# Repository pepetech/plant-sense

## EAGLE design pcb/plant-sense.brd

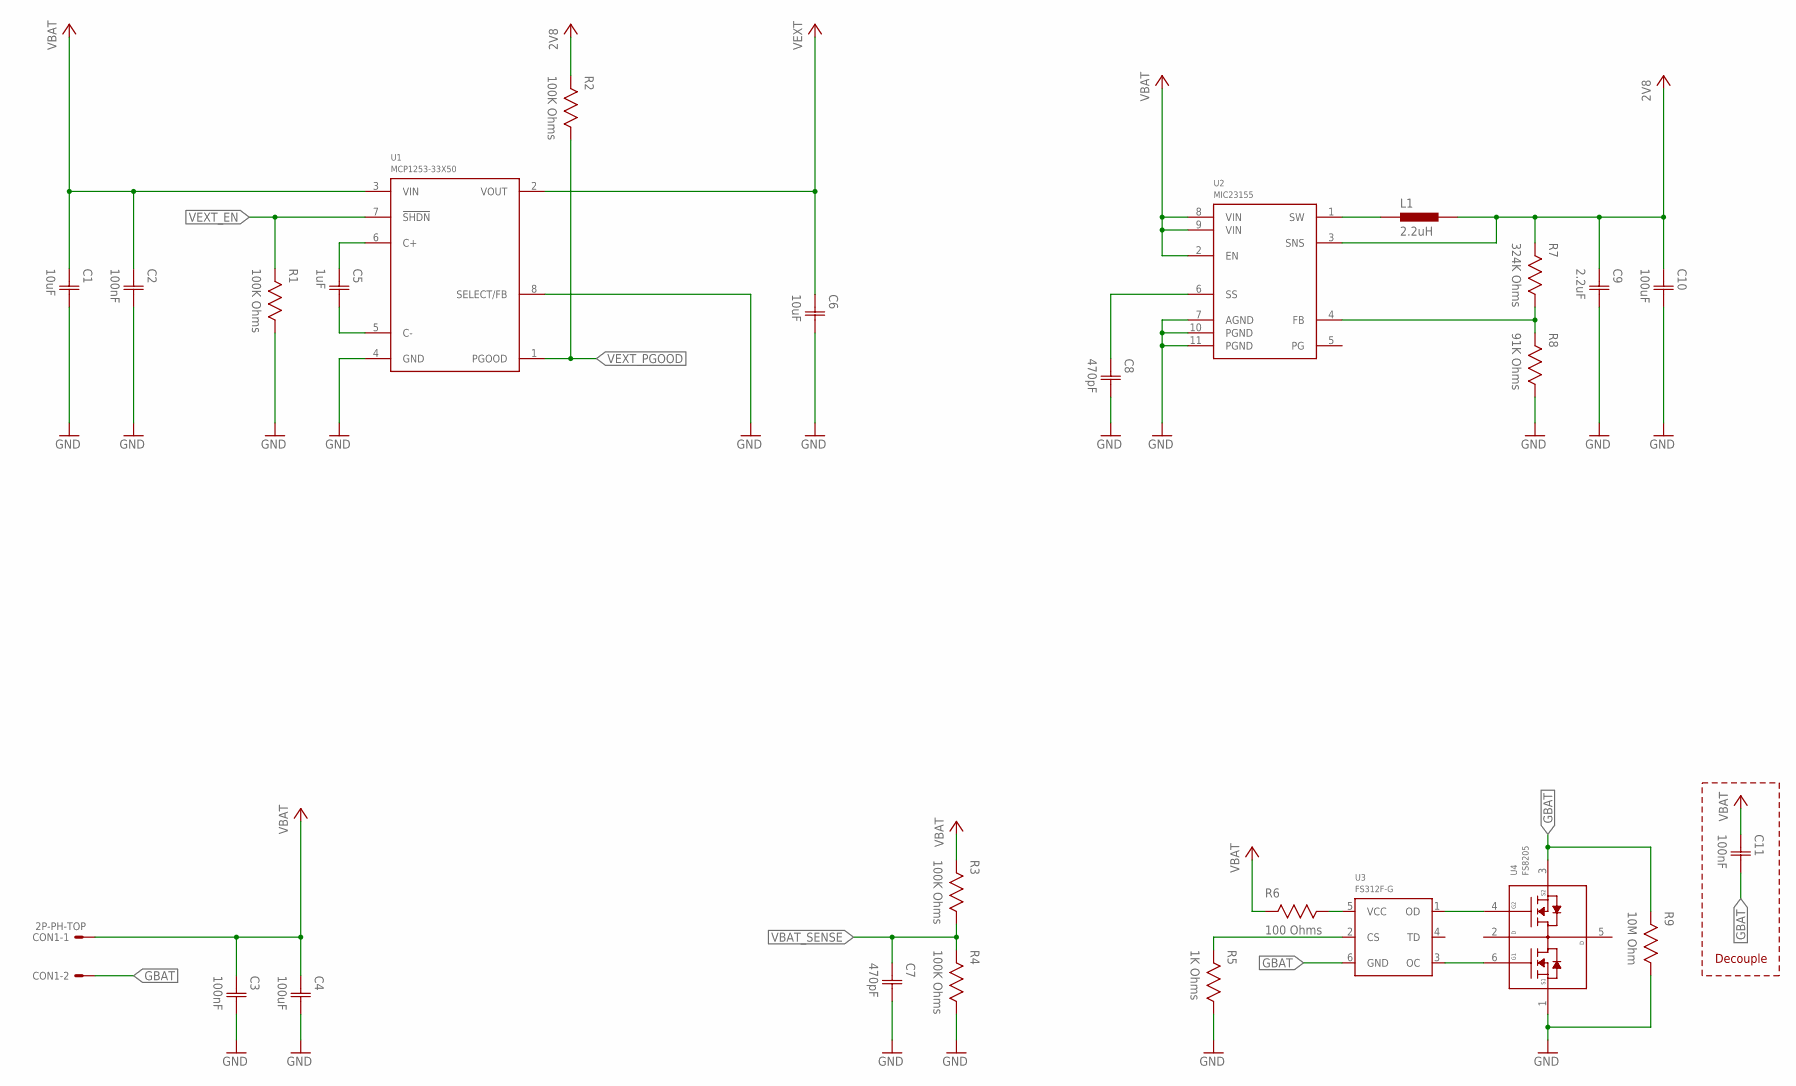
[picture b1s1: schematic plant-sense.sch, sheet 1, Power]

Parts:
C1, C6: 10uF; CAP0603
C2, C3, C11: 100nF; CAP0603
C4, C10: 100uF; CAP1206
C5: 1uF; CAP0603
C7, C8: 470pF; CAP0603
C9: 2.2uF; CAP0603
CON1: 2P-PH-TOP; PH-02-TOP
L1: 2.2uH; IND0805
R1, R2, R3, R4: 100K Ohms; RES0603
R5: 1K Ohms; RES0603
R6: 100 Ohms; RES0603
R7: 324K Ohms; RES0603
R8: 91K Ohms; RES0603
R9: 10M Ohm; RES0603
U1: MCP1253-33X50; MSOP8
U2: MIC23155; DFN10
U3: FS312F-G; SOT23-6
U4: FS8205; SOT23-6

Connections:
2V8: C9.1 (C1), C10.1 (C1), L1.2, R2.2, R7.2, U2.3 (SNS); also elsewhere on the board
GBAT: C11.2 (C2), CON1.2, R9.2, U3.6 (GND), U4.3 (S2)
GND: C1.2 (C2), C2.2 (C2), C3.2 (C2), C4.2 (C2), C6.2 (C2), C7.2 (C2), C8.2 (C2), C9.2 (C2), C10.2 (C2), R1.1, R4.1, R5.1, R8.1, R9.1, U1.4 (GND), U1.8 (SELECT/FB), U2.7 (AGND), U2.10 (PGND), U2.11 (PGND), U4.1 (S1); also elsewhere on the board
unnamed: C5.2 (C2), U1.5 (C-)
unnamed: C5.1 (C1), U1.6 (C+)
unnamed: L1.1, U2.1 (SW)
unnamed: R7.1, R8.2, U2.4 (FB)
unnamed: C8.1 (C1), U2.6 (SS)
unnamed: U3.3 (OC), U4.6 (G1)
unnamed: U3.1 (OD), U4.4 (G2)
unnamed: R6.1, U3.5 (VCC)
unnamed: R5.2, U3.2 (CS)
VBAT: C1.1 (C1), C2.1 (C1), C3.1 (C1), C4.1 (C1), C11.1 (C1), CON1.1, R3.2, R6.2, U1.3 (VIN), U2.2 (EN), U2.8 (VIN), U2.9 (VIN)
VBAT_SENSE: C7.1 (C1), R3.1, R4.2; also elsewhere on the board
VEXT: C6.1 (C1), U1.2 (VOUT); also elsewhere on the board
VEXT_EN: R1.2, U1.7 (!SHDN); also elsewhere on the board
VEXT_PGOOD: R2.1, U1.1 (PGOOD); also elsewhere on the board

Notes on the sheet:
Decouple

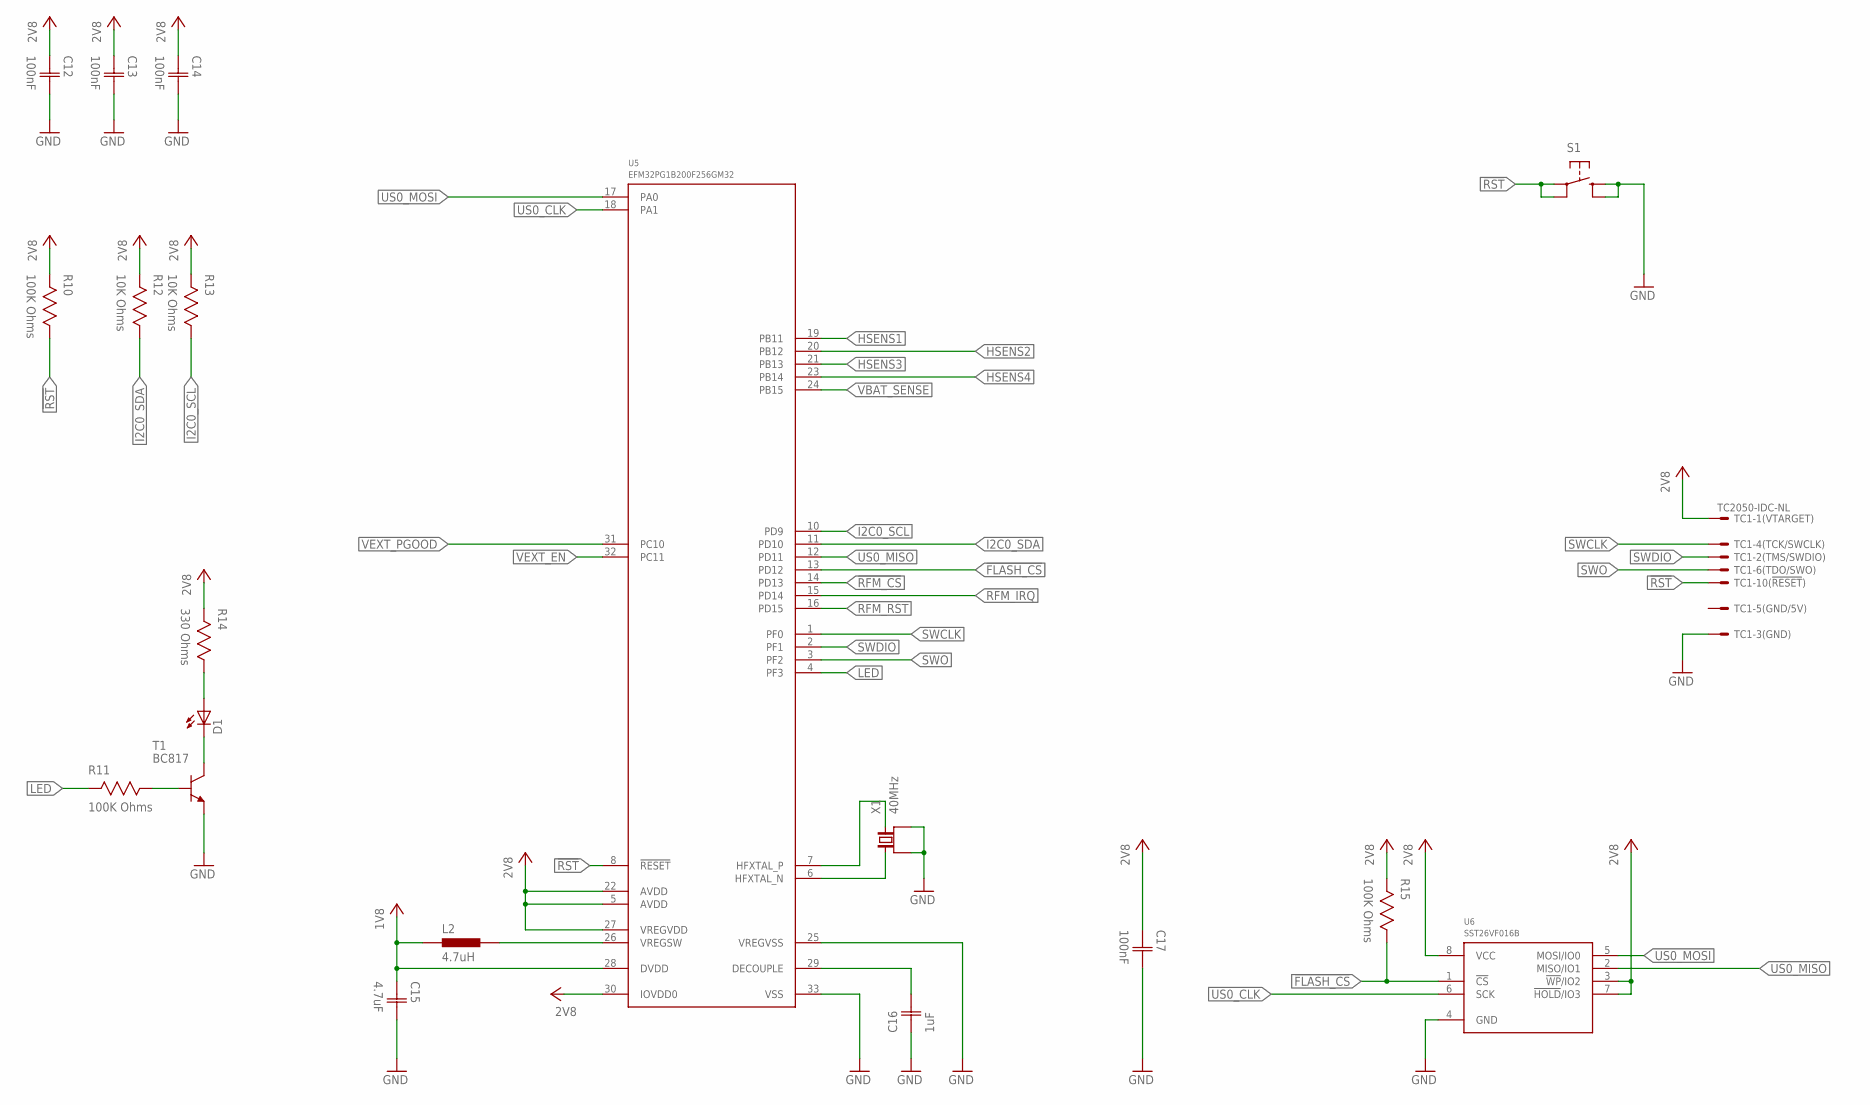
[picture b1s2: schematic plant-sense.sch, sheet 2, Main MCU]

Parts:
C12, C13, C14, C17: 100nF; CAP0603
C15: 4.7uF; CAP0603
C16: 1uF; CAP0603
D1: LED1206; 1206
L2: 4.7uH; IND0603
R10, R11, R15: 100K Ohms; RES0603
R12, R13: 10K Ohms; RES0603
R14: 330 Ohms; RES0603
S1: TAC_SWITCHSMD; TAC_SW_SMD_RESET
T1: BC817; SOT23
TC1: TC2050-IDC-NL
U5: EFM32PG1B200F256GM32; QFN32_0.5P
U6: SST26VF016B; WSOIC8
X1: 40MHz; 4-SMD-3225

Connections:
1V8: C15.1 (C1), L2.1, U5.28 (DVDD)
2V8: C12.1 (C1), C13.1 (C1), C14.1 (C1), C17.1 (C1), R10.2, R12.2, R13.2, R14.2, R15.2, TC1.1, U5.5 (AVDD), U5.22 (AVDD), U5.27 (VREGVDD), U5.30 (IOVDD0), U6.3 (!WP!/IO2), U6.7 (!HOLD!/IO3), U6.8 (VCC); also elsewhere on the board
!FLASH_CS: R15.1, U5.13 (PD12), U6.1 (!CS!)
!RFM_CS: U5.14 (PD13); also elsewhere on the board
!RST: R10.1, S1.1, S1.2, TC1.10, U5.8 (!RESET)
GND: C12.2 (C2), C13.2 (C2), C14.2 (C2), C15.2 (C2), C16.1 (C1), C17.2 (C2), S1.3, S1.4, T1.2 (E), TC1.3, U5.25 (VREGVSS), U5.33 (VSS), U6.4 (GND), X1.1 (GND), X1.3 (GND); also elsewhere on the board
HSENS1: U5.19 (PB11); also elsewhere on the board
HSENS2: U5.20 (PB12); also elsewhere on the board
HSENS3: U5.21 (PB13); also elsewhere on the board
HSENS4: U5.23 (PB14); also elsewhere on the board
I2C0_SCL: R13.1, U5.10 (PD9); also elsewhere on the board
I2C0_SDA: R12.1, U5.11 (PD10); also elsewhere on the board
LED: R11.2, U5.4 (PF3)
unnamed: R11.1, T1.1 (B)
unnamed: D1.C, T1.3 (C)
unnamed: U5.6 (HFXTAL_N), X1.2 (1)
unnamed: U5.7 (HFXTAL_P), X1.4 (2)
unnamed: D1.A, R14.1
unnamed: L2.2, U5.26 (VREGSW)
unnamed: C16.2 (C2), U5.29 (DECOUPLE)
RFM_IRQ: U5.15 (PD14); also elsewhere on the board
RFM_RST: U5.16 (PD15); also elsewhere on the board
SWCLK: TC1.4, U5.1 (PF0)
SWDIO: TC1.2, U5.2 (PF1)
SWO: TC1.6, U5.3 (PF2)
US0_CLK: U5.18 (PA1), U6.6 (SCK); also elsewhere on the board
US0_MISO: U5.12 (PD11), U6.2 (MISO/IO1); also elsewhere on the board
US0_MOSI: U5.17 (PA0), U6.5 (MOSI/IO0); also elsewhere on the board
VBAT_SENSE: U5.24 (PB15); also elsewhere on the board
VEXT_EN: U5.32 (PC11); also elsewhere on the board
VEXT_PGOOD: U5.31 (PC10); also elsewhere on the board

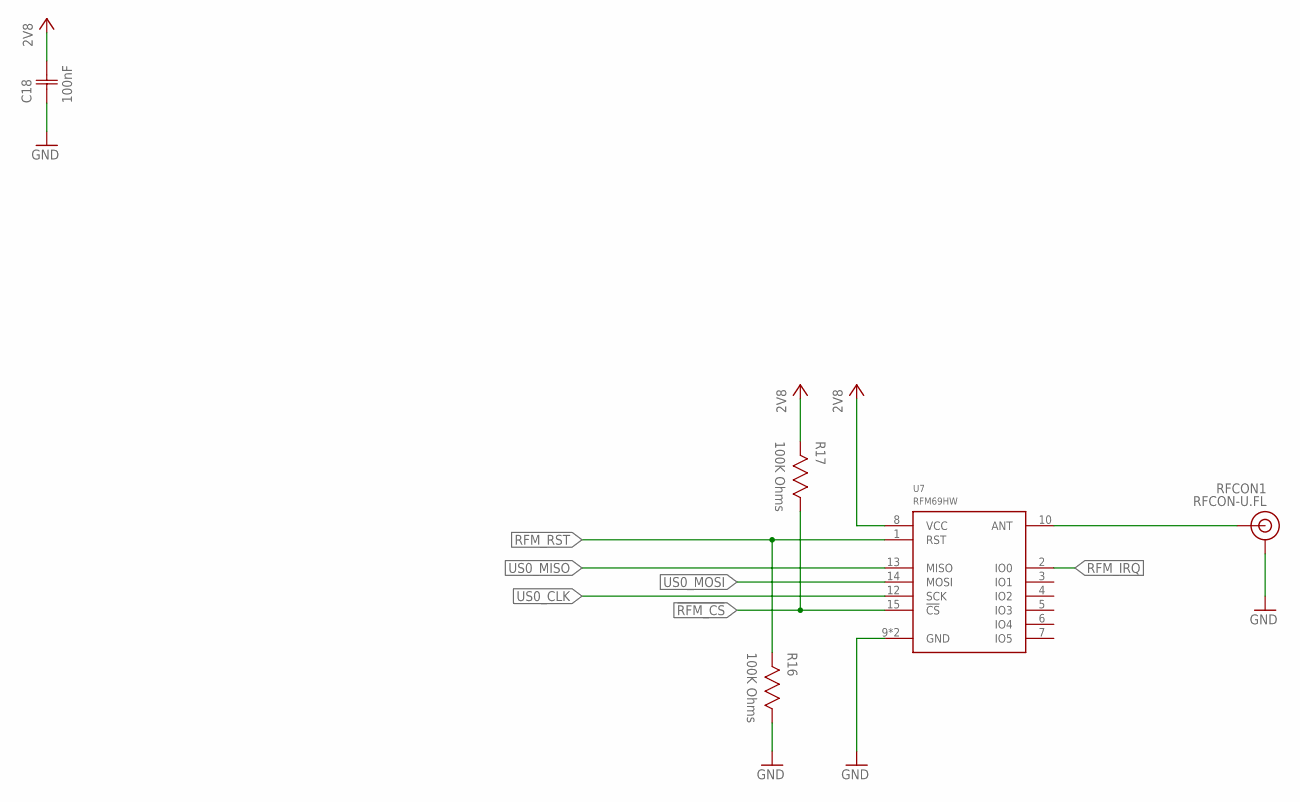
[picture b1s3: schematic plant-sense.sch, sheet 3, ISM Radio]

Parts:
C18: 100nF; CAP0603
R16, R17: 100K Ohms; RES0603
RFCON1: RFCON-U.FL; U.FL
U7: RFM69HW; RFM69XW-XXXS2

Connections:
2V8: C18.2 (C2), R17.2, U7.8 (VCC); also elsewhere on the board
!RFM_CS: R17.1, U7.15 (!CS); also elsewhere on the board
GND: C18.1 (C1), R16.1, RFCON1.P$1 (GND), RFCON1.P$2 (GND), U7.9 (GND), U7.11 (GND); also elsewhere on the board
unnamed: RFCON1.P$3 (SIGNAL), U7.10 (ANT)
RFM_IRQ: U7.2 (IO0); also elsewhere on the board
RFM_RST: R16.2, U7.1 (RST); also elsewhere on the board
US0_CLK: U7.12 (SCK); also elsewhere on the board
US0_MISO: U7.13 (MISO); also elsewhere on the board
US0_MOSI: U7.14 (MOSI); also elsewhere on the board

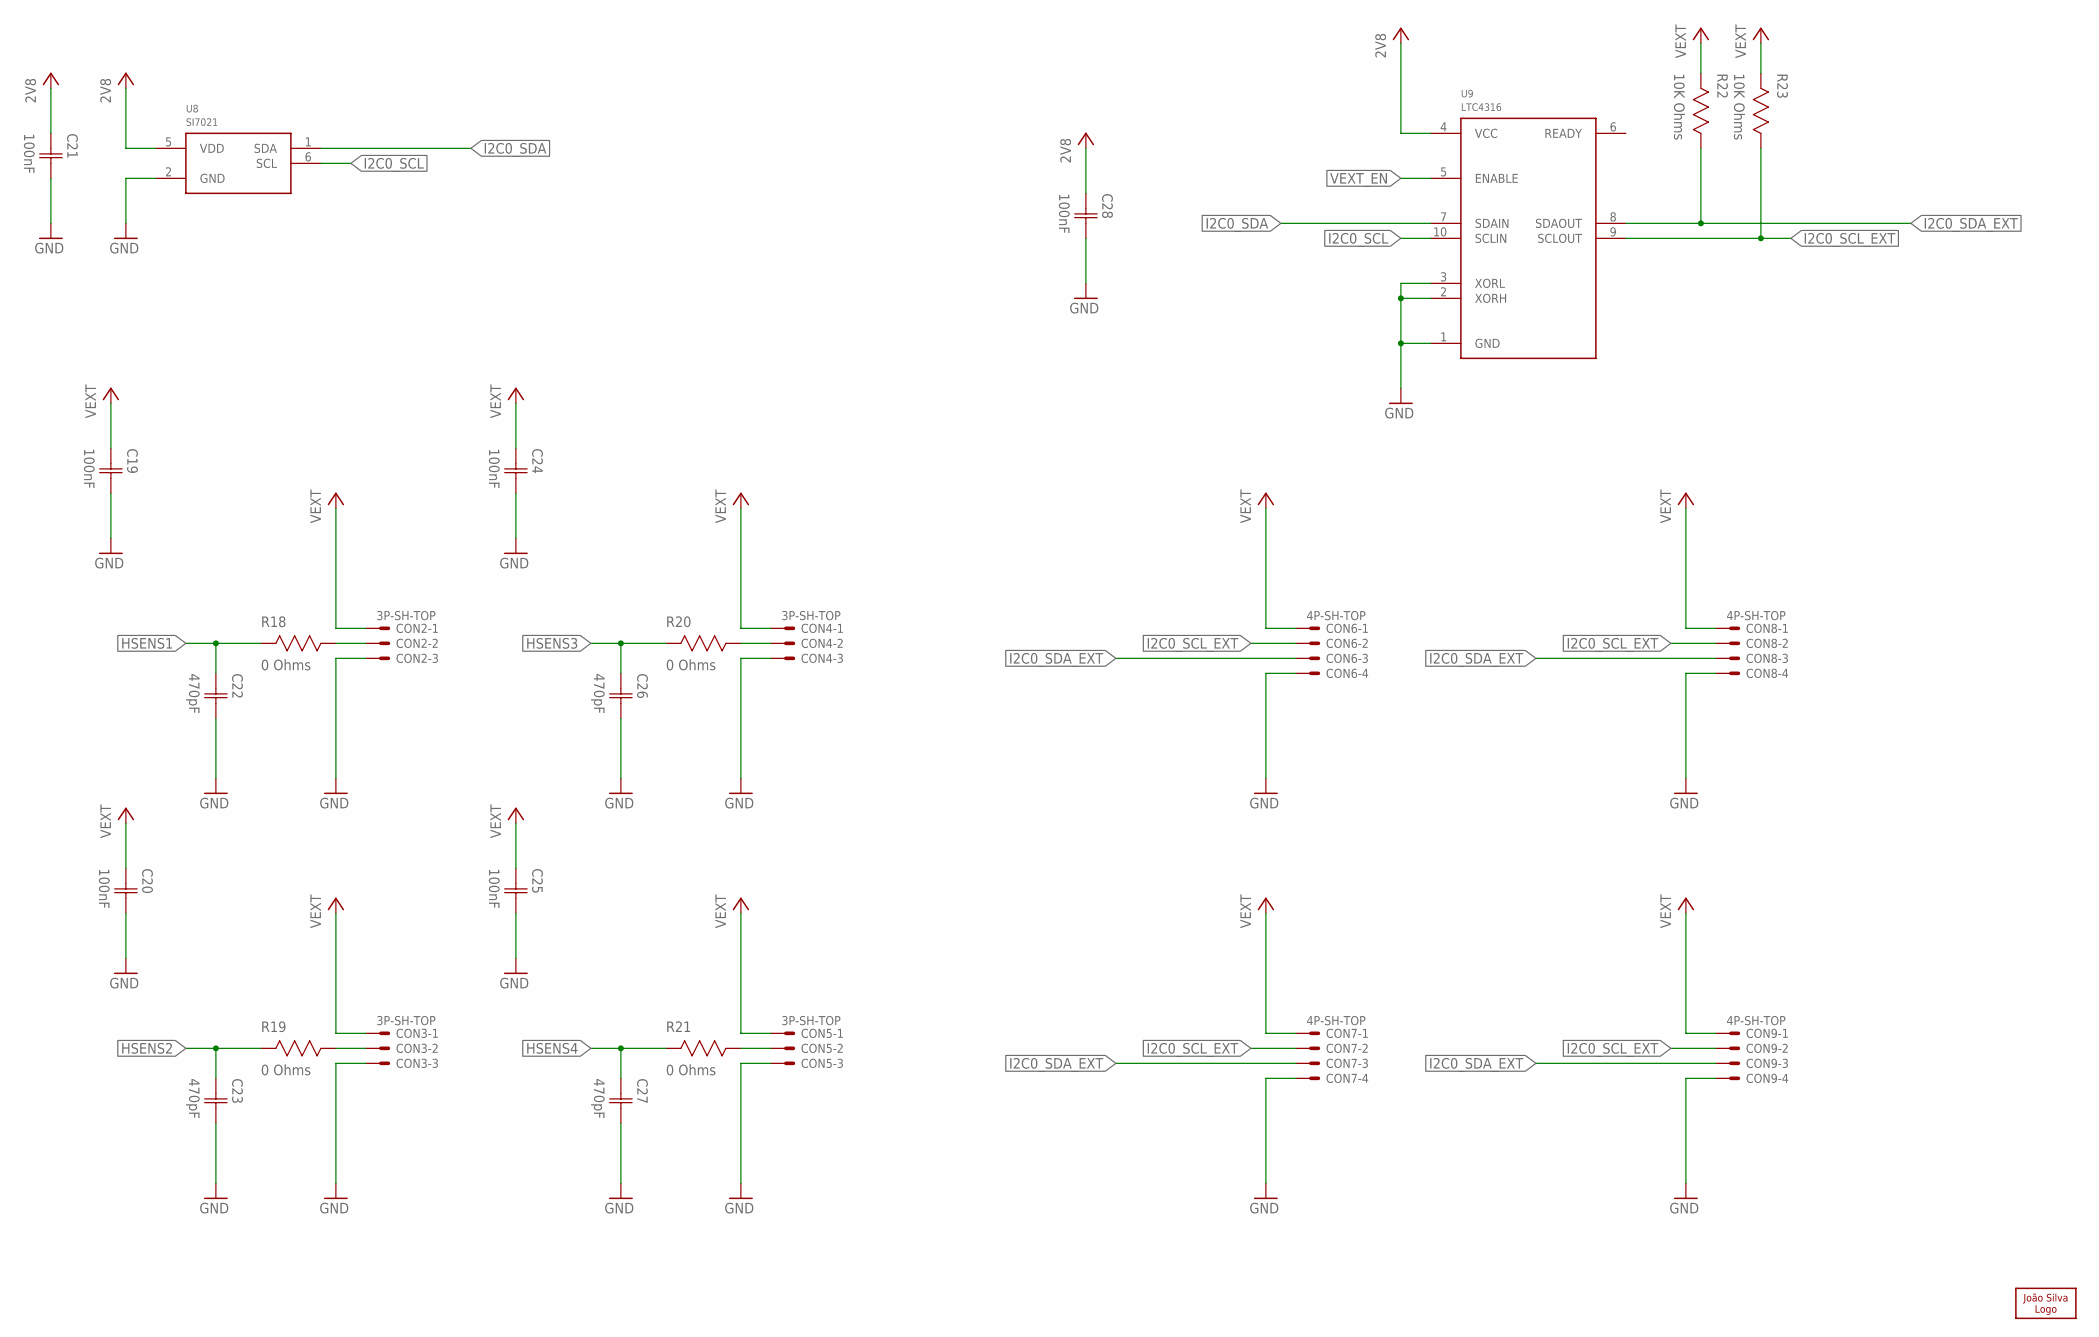
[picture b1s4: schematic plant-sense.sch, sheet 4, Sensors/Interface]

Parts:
C19, C20, C21, C24, C25, C28: 100nF; CAP0603
C22, C23, C26, C27: 470pF; CAP0603
CON2, CON3, CON4, CON5: 3P-SH-TOP; SH-03-TOP
CON6, CON7, CON8, CON9: 4P-SH-TOP; SH-04-TOP
LOGO1: JS-5MM; JS_5MM
R18, R19, R20, R21: 0 Ohms; RES0603
R22, R23: 10K Ohms; RES0603
U8: SI7021; DFN6
U9: LTC4316; MSOP10

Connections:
2V8: C21.1 (C1), C28.1 (C1), U8.5 (VDD), U9.4 (VCC); also elsewhere on the board
GND: C19.2 (C2), C20.2 (C2), C21.2 (C2), C22.2 (C2), C23.2 (C2), C24.2 (C2), C25.2 (C2), C26.2 (C2), C27.2 (C2), C28.2 (C2), CON2.3, CON3.3, CON4.3, CON5.3, CON6.4, CON7.4, CON8.4, CON9.4, U8.2 (GND), U9.1 (GND), U9.2 (XORH), U9.3 (XORL); also elsewhere on the board
HSENS1: C22.1 (C1), R18.2; also elsewhere on the board
HSENS2: C23.1 (C1), R19.2; also elsewhere on the board
HSENS3: C26.1 (C1), R20.2; also elsewhere on the board
HSENS4: C27.1 (C1), R21.2; also elsewhere on the board
I2C0_SCL: U8.6 (SCL), U9.10 (SCLIN); also elsewhere on the board
I2C0_SCL_EXT: CON6.2, CON7.2, CON8.2, CON9.2, R23.1, U9.9 (SCLOUT)
I2C0_SDA: U8.1 (SDA), U9.7 (SDAIN); also elsewhere on the board
I2C0_SDA_EXT: CON6.3, CON7.3, CON8.3, CON9.3, R22.1, U9.8 (SDAOUT)
unnamed: CON3.2, R19.1
unnamed: CON4.2, R20.1
unnamed: CON2.2, R18.1
unnamed: CON5.2, R21.1
VEXT: C19.1 (C1), C20.1 (C1), C24.1 (C1), C25.1 (C1), CON2.1, CON3.1, CON4.1, CON5.1, CON6.1, CON7.1, CON8.1, CON9.1, R22.2, R23.2; also elsewhere on the board
VEXT_EN: U9.5 (ENABLE); also elsewhere on the board

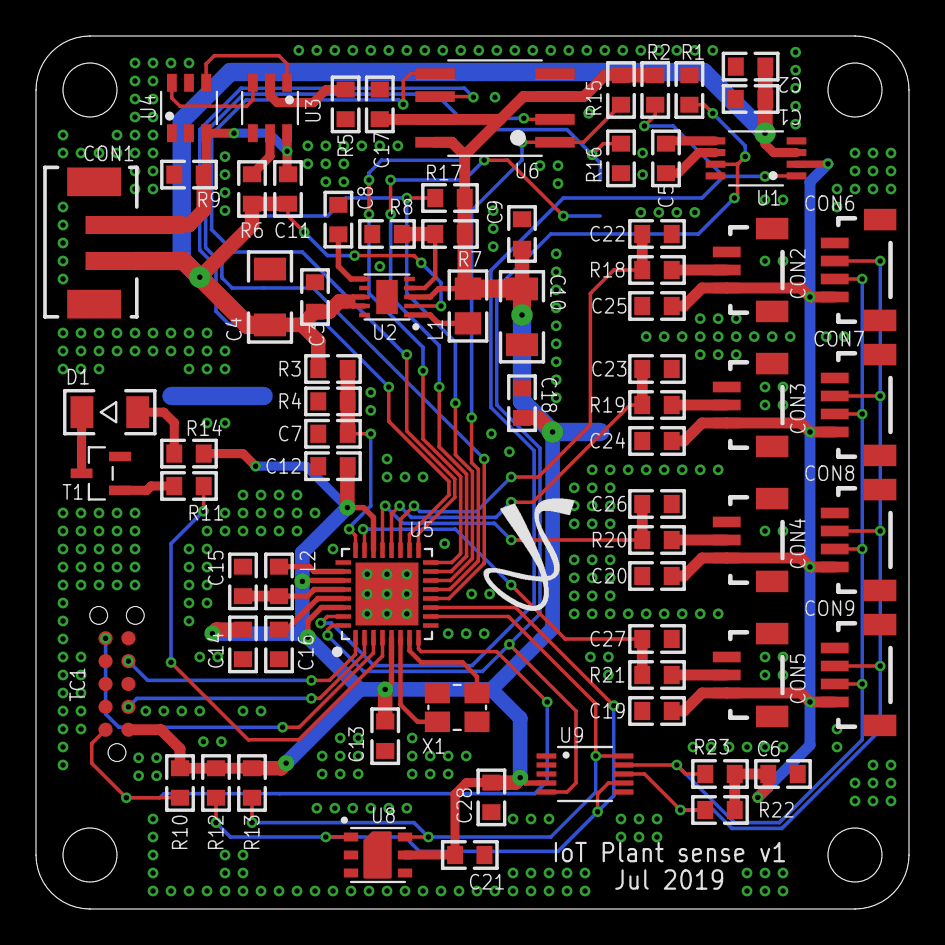
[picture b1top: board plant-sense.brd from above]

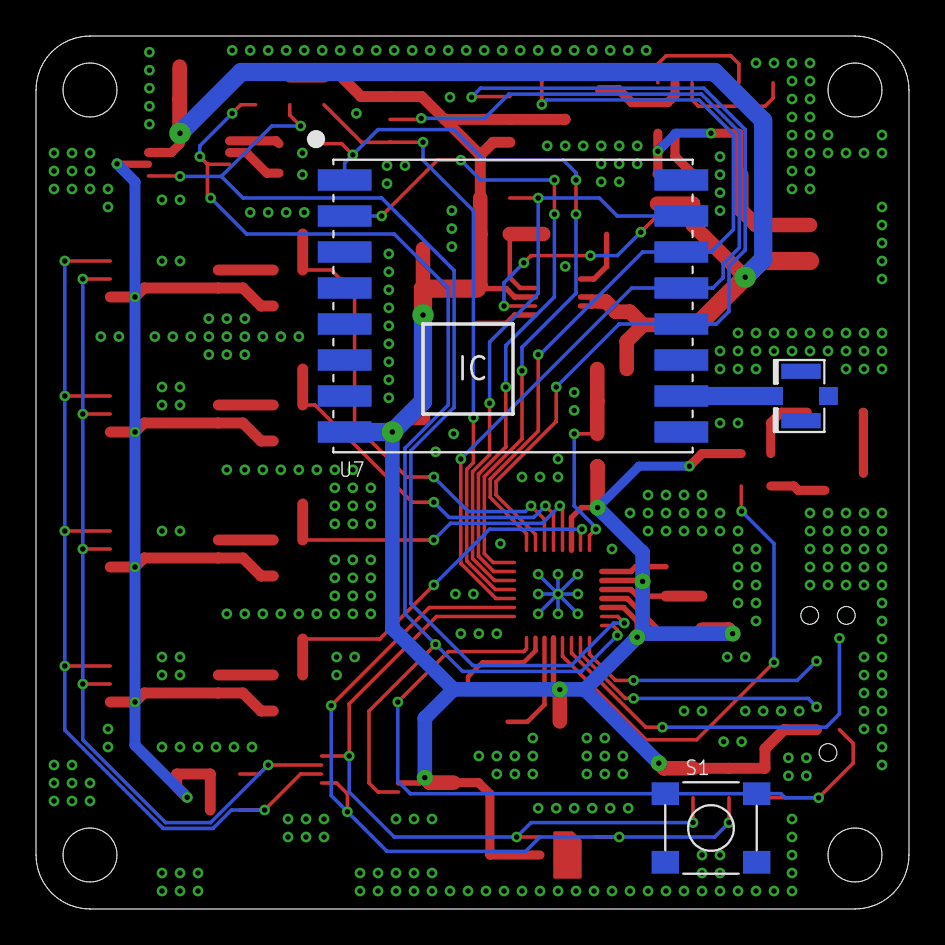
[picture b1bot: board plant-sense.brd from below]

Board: 2 copper layers, 48.5 x 48.5 mm, 78 parts (3 on the bottom side), 50 nets.

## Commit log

2019-05-27 Schematic work
2019-05-29 Work
2019-05-29 pcb work
2019-07-06 Change DRCs
2019-07-24 Finish board (needs revision)
2019-07-28 Finish machine gun
2019-10-07 Changed DRC Fixed overlapping traces
2019-11-10 Finish silk screen and generate gerbers
2019-12-30 Sync library updates Add schematic PDF
